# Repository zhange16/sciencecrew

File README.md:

# sciencecrew
Husky Robotics, Science Subsystem

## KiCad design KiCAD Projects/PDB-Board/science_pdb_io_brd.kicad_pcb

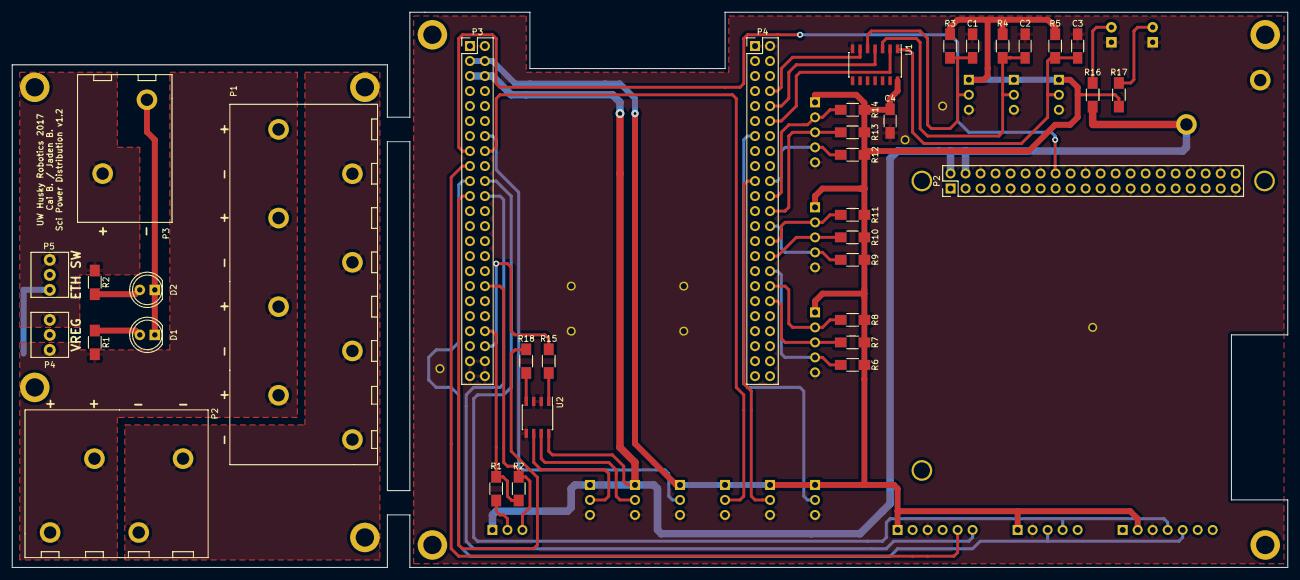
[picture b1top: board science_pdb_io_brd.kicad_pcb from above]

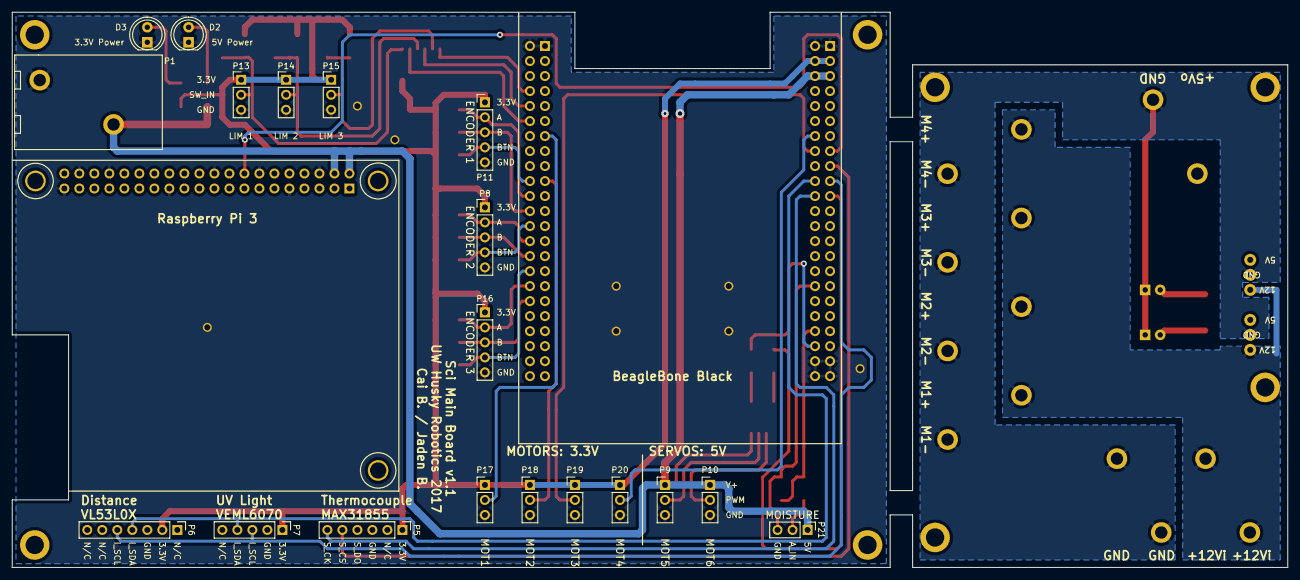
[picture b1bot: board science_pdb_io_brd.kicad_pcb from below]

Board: 2 copper layers, 215.9 x 94.0 mm, 59 parts (19 on the bottom side), 41 nets.

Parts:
C1, C2, C3: 1μF; C_1206_HandSoldering
C4: 100nF; C_1206_HandSoldering
D1, D2, D2#2, D3: LED; LED_D5.0mm
HL1, HL2, HL3, HL4: HOLE; HOLE_M3
P1: PWR_IN; PHOENIX_1792229
P1#2: MOTOR_PWR_OUT; PHOENIX_1792287
P2: RPI_HEADER; Pin_Header_Straight_2x20_Pitch2.54mm
P2#2: MAIN_PWR_IN; PHOENIX_1792245
P3: BBB_P9_HEADER; Pin_Header_Straight_2x23_Pitch2.54mm
P3#2: 5V_OUT; PHOENIX_1792229
P4: BBB_P8_HEADER; Pin_Header_Straight_2x23_Pitch2.54mm
P4#2: PWR_REG; MOLEX_0022232031
P5: THERMO_SENS; Pin_Header_Straight_1x06_Pitch2.54mm
P5#2: ETH_SWITCH; MOLEX_0022232031
P6: DIST_SENS; Pin_Header_Straight_1x07_Pitch2.54mm
P7: UV_SENS; Pin_Header_Straight_1x05_Pitch2.54mm
P8: ENCODER_2; Pin_Header_Straight_1x05_Pitch2.54mm
P9: MOTOR5_PWM; Pin_Header_Straight_1x03_Pitch2.54mm
P10: MOTOR6_PWM; Pin_Header_Straight_1x03_Pitch2.54mm
P11: ENCODER_1; Pin_Header_Straight_1x05_Pitch2.54mm
P13: LIMIT1_IN; Pin_Header_Straight_1x03_Pitch2.54mm
P14: LIMIT2_IN; Pin_Header_Straight_1x03_Pitch2.54mm
P15: LIMIT3_IN; Pin_Header_Straight_1x03_Pitch2.54mm
P16: ENCODER_3; Pin_Header_Straight_1x05_Pitch2.54mm
P17: MOTOR1_PWM; Pin_Header_Straight_1x03_Pitch2.54mm
P18: MOTOR2_PWM; Pin_Header_Straight_1x03_Pitch2.54mm
P19: MOTOR3_PWM; Pin_Header_Straight_1x03_Pitch2.54mm
P20: MOTOR4_PWM; Pin_Header_Straight_1x03_Pitch2.54mm
P21: MOISTURE_CONN; Pin_Header_Straight_1x03_Pitch2.54mm
R1: 1kΩ; R_1206_HandSoldering
R1#2, R2#2: R; R_1206_HandSoldering
R2: 560Ω; R_1206_HandSoldering
R3, R4, R5, R6, R7, R8, R9, R10, R11, R12, R13, R14: 5kΩ; R_1206_HandSoldering
R15, R18: 300Ω; R_1206_HandSoldering
R16: 180Ω; R_1206_HandSoldering
R17: 80Ω; R_1206_HandSoldering
U1: SN74HC14N; SOIC-14_3.9x8.7mm_Pitch1.27mm
U2: ACPL-064L-500E; SOIC-8_3.9x4.9mm_Pitch1.27mm

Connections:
+3V3: C4.1, P3.3, P3.4, P5.1, P6.2, P7.1, P8.1, P11.1, P13.1, P14.1, P15.1, P16.1, P17.1, P18.1, P19.1, P20.1, R3.2, R4.2, R5.2, R6.1, R7.1, R8.1, R9.1, R10.1, R11.1, R12.1, R13.1, R14.1, R17.1, U1.14
+5V: P1.2, P2.2, P2.4, P3.5, P3.6, P3#2.2, P4#2.3, P5#2.3, P9.1, P10.1, P21.1, R2#2.1, R16.1, U2.8
+12V: P1#2.2, P1#2.4, P1#2.6, P1#2.8, P2#2.1, P2#2.2, P4#2.1, P5#2.1, R1#2.1
/B_LIM1: C3.2, P13.2, R5.1, U1.1
/B_LIM2: C2.2, P14.2, R4.1, U1.3
/B_LIM3: C1.2, P15.2, R3.1, U1.5
/CAM_TRIG: P2.16, P3.15
/ENC1_A: P4.22, P11.2, R14.2
/ENC1_B: P4.24, P11.3, R13.2
/ENC1_BUT: P4.20, P11.4, R12.2
/ENC2_A: P4.28, P8.2, R11.2
/ENC2_B: P4.30, P8.3, R10.2
/ENC2_BUT: P4.26, P8.4, R9.2
/ENC3_A: P4.34, P16.2, R8.2
/ENC3_B: P4.36, P16.3, R7.2
/ENC3_BUT: P4.32, P16.4, R6.2
/I2C_SCL: P3.19, P6.5, P7.3
/I2C_SDA: P3.20, P6.4, P7.4
/LIMIT1_IN: P4.12, U1.2
/LIMIT2_IN: P4.10, U1.4
/LIMIT3_IN: P4.8, U1.6
/MOISTURE_IN: P3.40, R1.2, R2.1
/MOTOR1_PWM: P4.13, P17.2
/MOTOR2_PWM: P4.19, P18.2
/MOTOR3_PWM: P3.16, P19.2
/MOTOR4_PWM: P3.14, P20.2
/MOTOR5_PWM: P3.42, R15.2
/MOTOR6_PWM: P3.21, R18.2
/SPI_CLK: P3.22, P5.6
/SPI_CS: P3.17, P5.5
GND: D1.1, D2#2.1, P1#2.1, P1#2.3, P1#2.5, P1#2.7, P2#2.3, P2#2.4, P3#2.1, P4#2.2, P5#2.2
GNDA: P3.34, P21.3, R2.2
GNDD: C1.1, C2.1, C3.1, C4.2, D2.1, D3.1, P1.1, P2.6, P2.9, P2.14, P2.20, P2.25, P2.34, P2.38, P2.39, P3.1, P3.2, P3.43, P3.44, P3.45, P3.46, P4.1, P4.2, P5.3, P6.3, P7.2, P8.5, P9.3, P10.3, P11.5, P13.3, P14.3, P15.3, P16.5, P17.3, P18.3, P19.3, P20.3, U1.7, U2.2, U2.3, U2.5
unnamed: D1.2, R1#2.2
unnamed: D2.2, D2#2.2, R2#2.2, R16.2
unnamed: D3.2, R17.2
unnamed: P9.2, U2.7
unnamed: P10.2, U2.6
unnamed: P21.2, R1.1
unnamed: R15.1, U2.1
unnamed: R18.1, U2.4

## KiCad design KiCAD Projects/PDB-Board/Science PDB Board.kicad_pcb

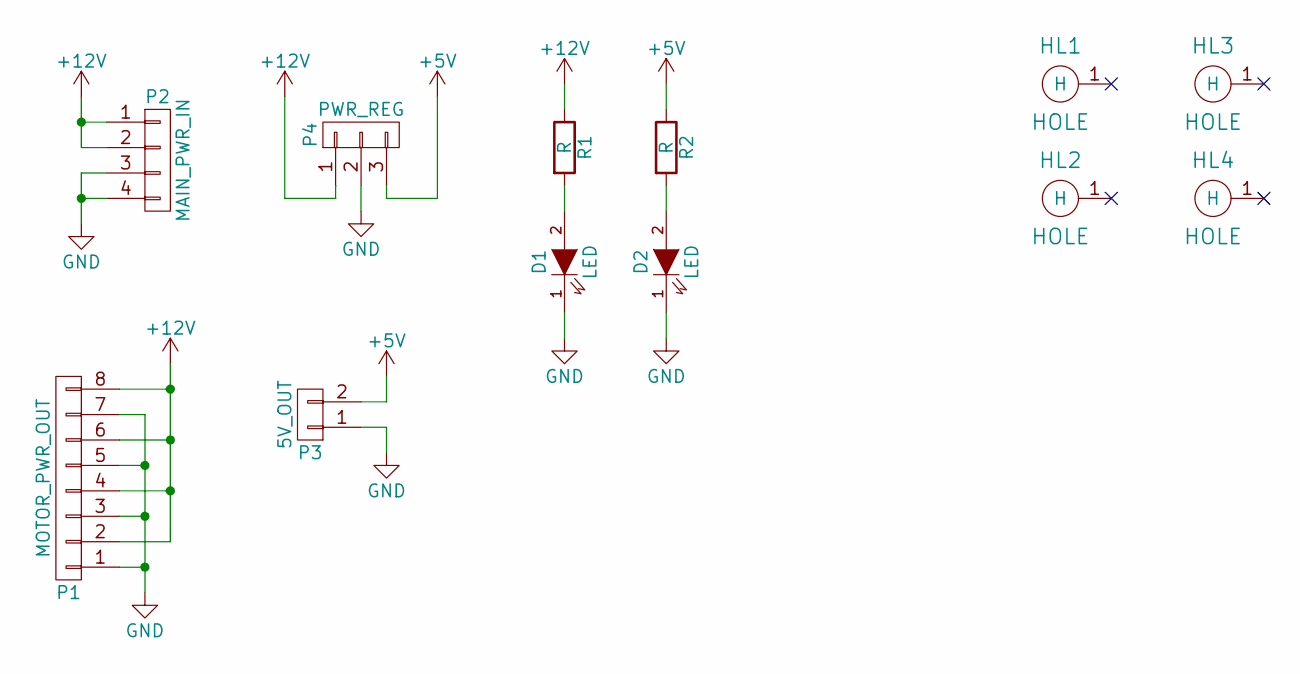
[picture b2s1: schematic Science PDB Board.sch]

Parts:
D1, D2: LED; LED_D5.0mm
HL1, HL2, HL3, HL4: HOLE; HOLE_M3
P1: MOTOR_PWR_OUT; PHOENIX_1792287
P2: MAIN_PWR_IN; PHOENIX_1792245
P3: 5V_OUT; PHOENIX_1792229
P4: PWR_REG; MOLEX_0022232031
R1, R2: R; R_1206_HandSoldering

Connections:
+5V: P3.2, P4.3, R2.1; also elsewhere on the board
+12V: P1.2, P1.4, P1.6, P1.8, P2.1, P2.2, P4.1, R1.1; also elsewhere on the board
GND: D1.1 (K), D2.1 (K), P1.1, P1.3, P1.5, P1.7, P2.3, P2.4, P3.1, P4.2; also elsewhere on the board
unnamed: D1.2 (A), R1.2
unnamed: D2.2 (A), R2.2

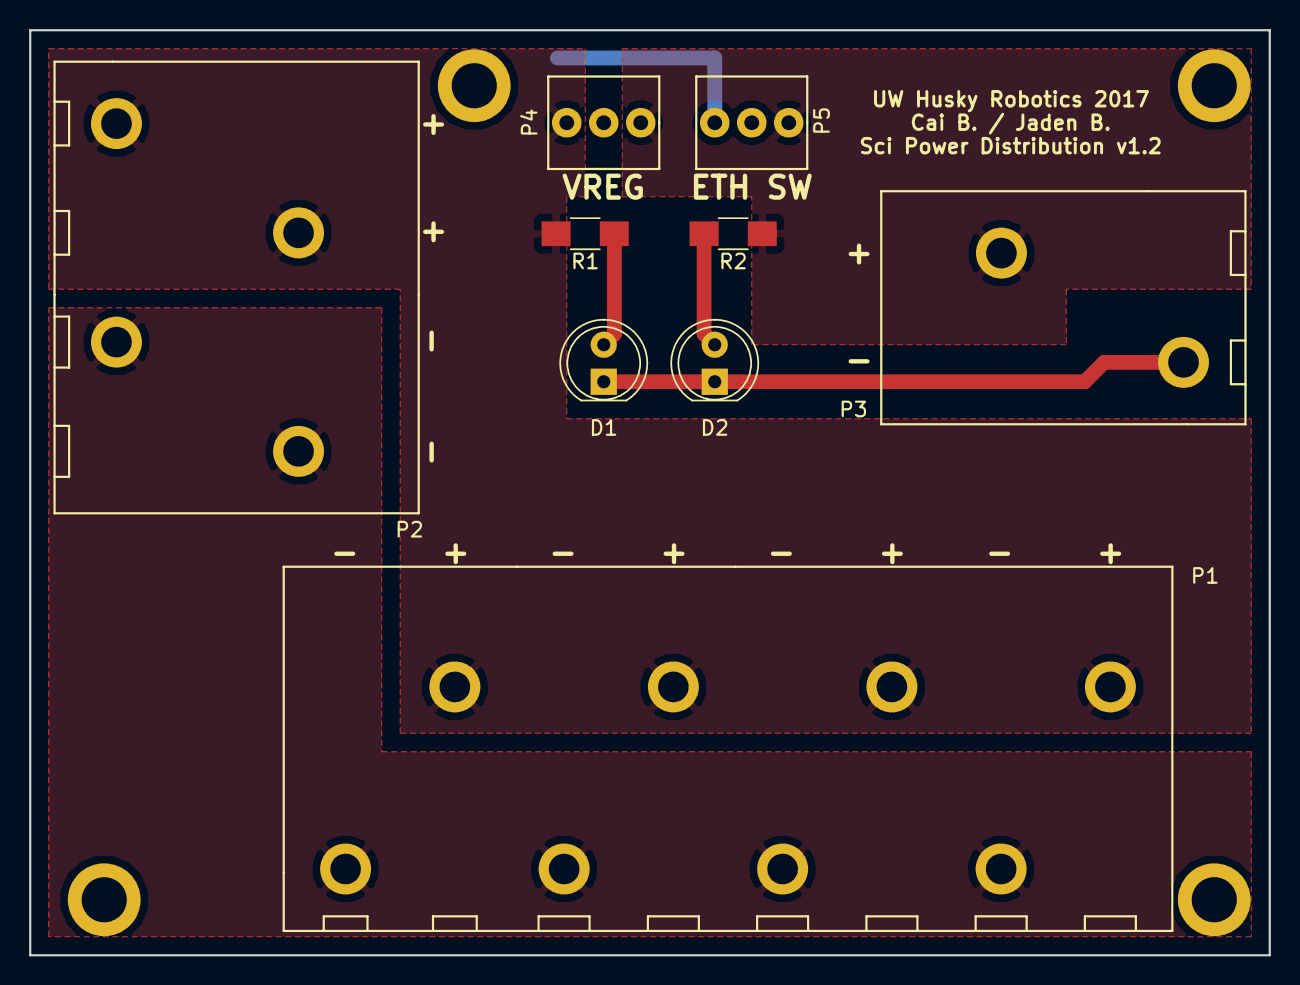
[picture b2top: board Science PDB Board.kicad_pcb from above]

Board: 2 copper layers, 85.1 x 63.5 mm, 13 parts (0 on the bottom side), 5 nets.

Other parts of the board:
P5: ETH_SWITCH; MOLEX_0022232031

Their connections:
+5V: P5.3; also elsewhere on the board
+12V: P5.1; also elsewhere on the board
GND: P5.2; also elsewhere on the board

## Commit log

2016-12-03 Upload Arduino files
    Files and data from testing humidity sensor, and a servo code
2017-01-10 Added Folders for KiCAD Projects & Sensor Code.
    I'll upload the sensor code later, when I have access to the BeagleBone.
2017-01-28 PDB-IObrd
2017-02-01 Added LS7366R to library
    Added spi encoder counter to KiCAD Library.
2017-02-01 Added more DIOs
2017-02-07 Changed board schematic
2017-02-07 Deleted backup file
2017-02-12 More schematic work
2017-02-12 Minor Schematic Tweaks
    No functional changes, just making the schematic look a little nicer.
2017-02-25 Board updates
2017-02-25 Fixed pinouts, started board layout.
2017-02-25 Worked on PCB
2017-02-28 Added Pullup Resistors to Encoder Channels
    Needs to look more pretty
2017-02-28 Created Better Pullup resistors
2017-02-28 Made temp values for RC LPF. Updated components
2017-03-04 Preparing for PCB Work
2017-03-04 Fixed net name labels
2017-03-04 Created Power Distribution Board. Moved stuff to it.
2017-03-05 Worked some more on Power Distribution Board
2017-03-20 Added Some Datasheets
2017-03-22 Made pin connetions for encoder
2017-04-01 Worked on PDB PCB
    Still needs mounting holes.
2017-04-02 Added Pi Headers and Power and ground
2017-04-04 Added current limiting resistors to 5V and 3.3V
    On IO board only
2017-04-08 Revert "Finished? PDB v2"
    This reverts commit a04adeda8b22dfbdd33fba7944ab085dcccc9394.
2017-04-08 Finished? PDB
2017-04-08 Finished? PDB v2
    Committing this that weren't?
2017-04-08 Revert "Revert "Finished? PDB v2""
    This reverts commit d801b87a72680285d22ac13d8543e7e2de8ff54b.
2017-04-08 Worked on Main Board
2017-04-08 Progrss on Main Board Layout
2017-04-08 Continued on Main PCB layout. Getting there.
2017-04-08 Last main PCB commit for now.
2017-04-08 Finished PDB. Actually.
    Sending for review.
2017-04-15 Had to change PWM channels
2017-04-22 Worked on PDB
    Added silkscreen and silkscreen cutout segmentation as per feedback from
    Justin.
2017-04-22 Finished working on PDB.
    Ready for another review.
2017-04-22 Progress on Main Board
2017-04-23 Main Board Layout Mostly Complete
    Still needs power routed, but everything else is pretty much finished
    now.
2017-04-23 Power Layout Mostly Done
    Just needs ground planes and a few tweaks.
2017-04-23 Main Board Almost Finished
    Needs via stitching between ground planes under BeagleBone, then
    everything should be connected and ready to go!
2017-04-23 Finished Getting Main Board Routed!
    Everything's connected together as it needs to be. Some minor tweaks,
    then off to revision!
2017-04-23 Main Board Ready for Review!
2017-04-25 Added Optocoupler and connections for 2 servos
2017-04-29 Made CHanges to Raspberry Pi
    These definitely are not wrong at all.
2017-04-29 Revert "Made CHanges to Raspberry Pi"
    This reverts commit 9b6c6e1ff9c729eb0e6bf7611c964737bcdfa00b.
2017-04-29 Started Fixing Errors
2017-04-29 Implemented Newest Revisions
2017-04-29 Finished Editing Connectors
    Increased spacing for Molex connectors.
2017-04-29 Added Package info for Optocoupler
    Forgot to add this to the last commit.
2017-04-30 Minor Updates
    Changed capacitors to resistors (all 1206 Rs were 1206 Cs). Small
    silkscreen changes.
2017-04-30 Submitting for Review.
2017-05-01 Minor changes to make board more manufacturable
2017-05-06 Added Ethernet switch power connector
2017-05-06 Final Version for Manufacturing
2017-05-07 Had to Change Encoder Pins Post-Manufacture
    The pins we intended to use do not work due to HDMI/eMMC
2017-05-14 Added info on AF testing
    I've been spending a few hours on testing autofocus algorithms, so I
    thought I'd put my findings in a spreadsheet, and put them here.
